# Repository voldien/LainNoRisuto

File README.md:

# LainNoRisuto

Just a collection of electronic schematic and board layouts.

## ARM ToolChain

```bash
```

## AVR ToolChain

```bash
sudo apt-get install gcc-avr binutils-avr avr-libc gdb-avr avrdude
```

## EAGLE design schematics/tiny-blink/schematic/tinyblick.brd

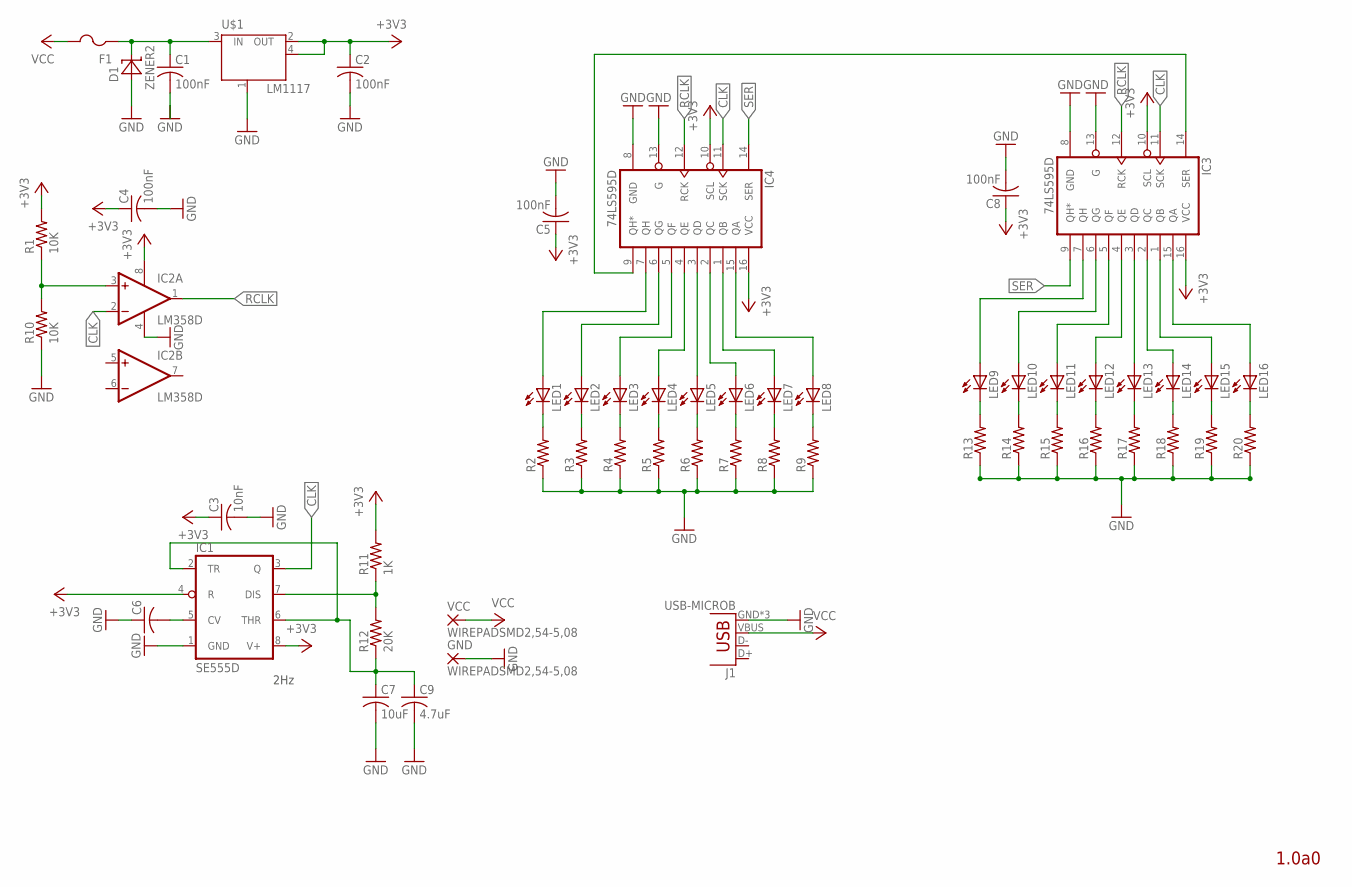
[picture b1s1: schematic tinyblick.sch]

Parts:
C1, C2, C4, C5, C8: 100nF; C0603
C3: 10nF; C0603
C6: C-USC0603; C0603
C7: 10uF; C0603
C9: 4.7uF; C0603
D1: ZENER2; SOD123
F1: PTCFUSE-1206; R1206
GND: WIREPADSMD2,54-5,08; SMD2,54-5,08
IC1: SE555D; SO08
IC2: LM358D; SO08
IC3, IC4: 74LS595D; SO16
J1: USB-MICROB
LED1, LED2, LED3, LED4, LED5, LED6, LED7, LED8, LED9, LED10, LED11, LED12, LED13, LED14, LED15, LED16: LEDCHIP-LED0603; CHIP-LED0603
R1, R10: 10K; R0603
R2, R3, R4, R5, R6, R7, R8, R9, R13, R14, R15, R16, R17, R18, R19, R20: R-US_R0603; R0603
R11: 1K; R0603
R12: 20K; R0603
U$1: LM1117; SOT223
VCC: WIREPADSMD2,54-5,08; SMD2,54-5,08

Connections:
+3V3: C2.1, C3.1, C4.1, C5.1, C8.1, IC1.4 (R), IC1.8 (V+), IC2.8 (V+), IC3.10 (SCL), IC3.16 (VCC), IC4.10 (SCL), IC4.16 (VCC), R1.2, R11.2, U$1.2 (OUT), U$1.4 (OUT)
CLK: IC1.3 (Q), IC2.2 (-IN), IC3.11 (SCK), IC4.11 (SCK)
GND: C1.2, C2.2, C3.2, C4.2, C5.2, C6.1, C7.2, C8.2, C9.2, D1.A, GND.1, IC1.1 (GND), IC2.4 (V-), IC3.8 (GND), IC3.13 (G), IC4.8 (GND), IC4.13 (G), J1.GND, J1.MT1 (GND), J1.MT2 (GND), R2.1, R3.1, R4.1, R5.1, R6.1, R7.1, R8.1, R9.1, R10.1, R13.1, R14.1, R15.1, R16.1, R17.1, R18.1, R19.1, R20.1, U$1.1 (GND/ADJ)
unnamed: LED1.C, R2.2
unnamed: IC1.7 (DIS), R11.1, R12.2
unnamed: LED2.C, R3.2
unnamed: C7.1, C9.1, IC1.2 (TR), IC1.6 (THR), R12.1
unnamed: LED3.C, R4.2
unnamed: LED9.C, R13.2
unnamed: LED4.C, R5.2
unnamed: LED5.C, R6.2
unnamed: IC4.3 (QD), LED5.A
unnamed: LED6.C, R7.2
unnamed: IC4.2 (QC), LED6.A
unnamed: LED7.C, R8.2
unnamed: IC4.1 (QB), LED7.A
unnamed: LED8.C, R9.2
unnamed: IC4.15 (QA), LED8.A
unnamed: IC4.7 (QH), LED1.A
unnamed: IC2.3 (+IN), R1.1, R10.2
unnamed: C1.1, D1.C, F1.1, U$1.3 (IN)
unnamed: IC4.6 (QG), LED2.A
unnamed: IC4.5 (QF), LED3.A
unnamed: C6.2, IC1.5 (CV)
unnamed: LED10.C, R14.2
unnamed: LED11.C, R15.2
unnamed: IC4.4 (QE), LED4.A
unnamed: LED12.C, R16.2
unnamed: LED13.C, R17.2
unnamed: IC3.3 (QD), LED13.A
unnamed: LED14.C, R18.2
unnamed: IC3.2 (QC), LED14.A
unnamed: LED15.C, R19.2
unnamed: IC3.1 (QB), LED15.A
unnamed: LED16.C, R20.2
unnamed: IC3.15 (QA), LED16.A
unnamed: IC3.7 (QH), LED9.A
unnamed: IC3.6 (QG), LED10.A
unnamed: IC3.5 (QF), LED11.A
unnamed: IC3.4 (QE), LED12.A
unnamed: IC3.14 (SER), IC4.9 (QH*)
RCLK: IC2.1 (OUT), IC3.12 (RCK), IC4.12 (RCK)
SER: IC3.9 (QH*), IC4.14 (SER)
VCC: F1.2, J1.VBUS, VCC.1

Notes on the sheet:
1.0a0
2Hz

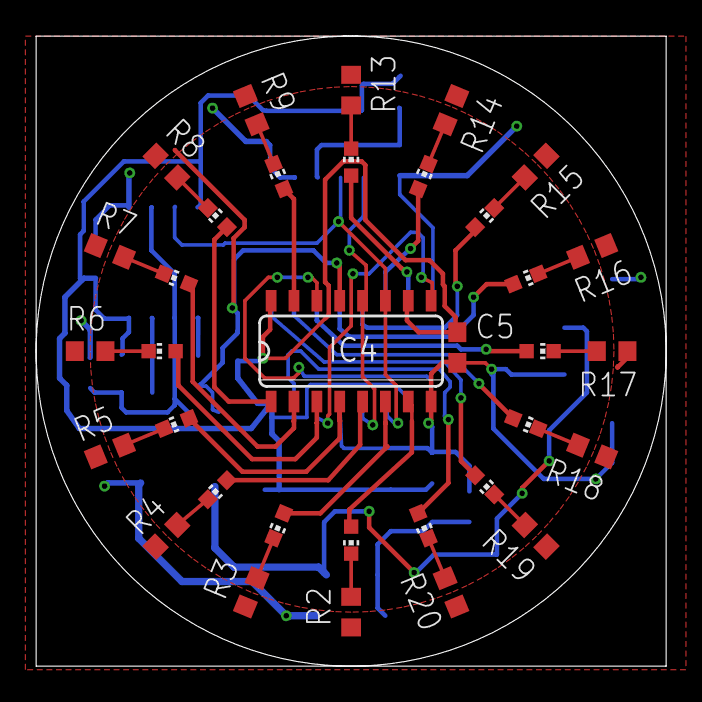
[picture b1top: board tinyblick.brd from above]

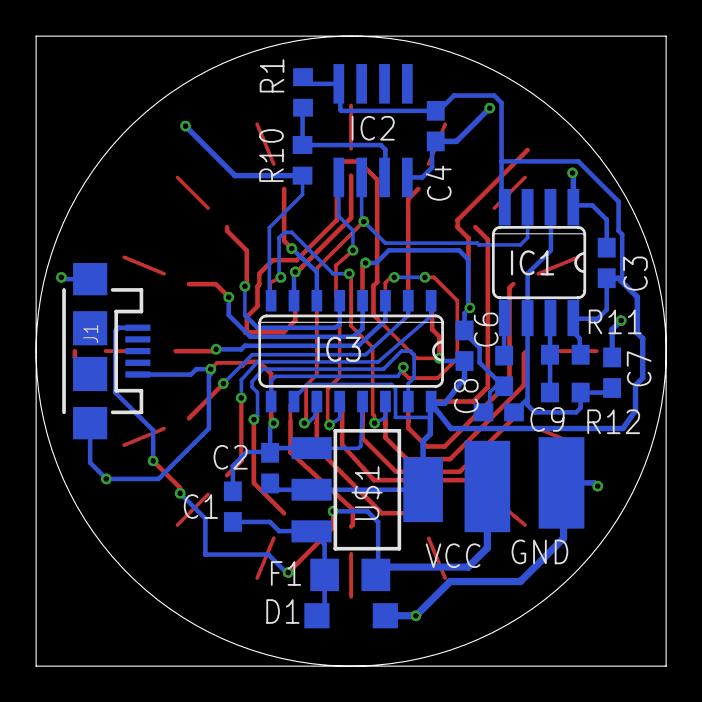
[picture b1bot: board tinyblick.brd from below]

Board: 2 copper layers, 35.0 x 35.0 mm, 55 parts (21 on the bottom side), 44 nets.

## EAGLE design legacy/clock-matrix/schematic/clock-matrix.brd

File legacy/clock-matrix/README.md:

# Binary Matrix Clock

Insipired by the binary clock in smarter every day.

## Board Layout

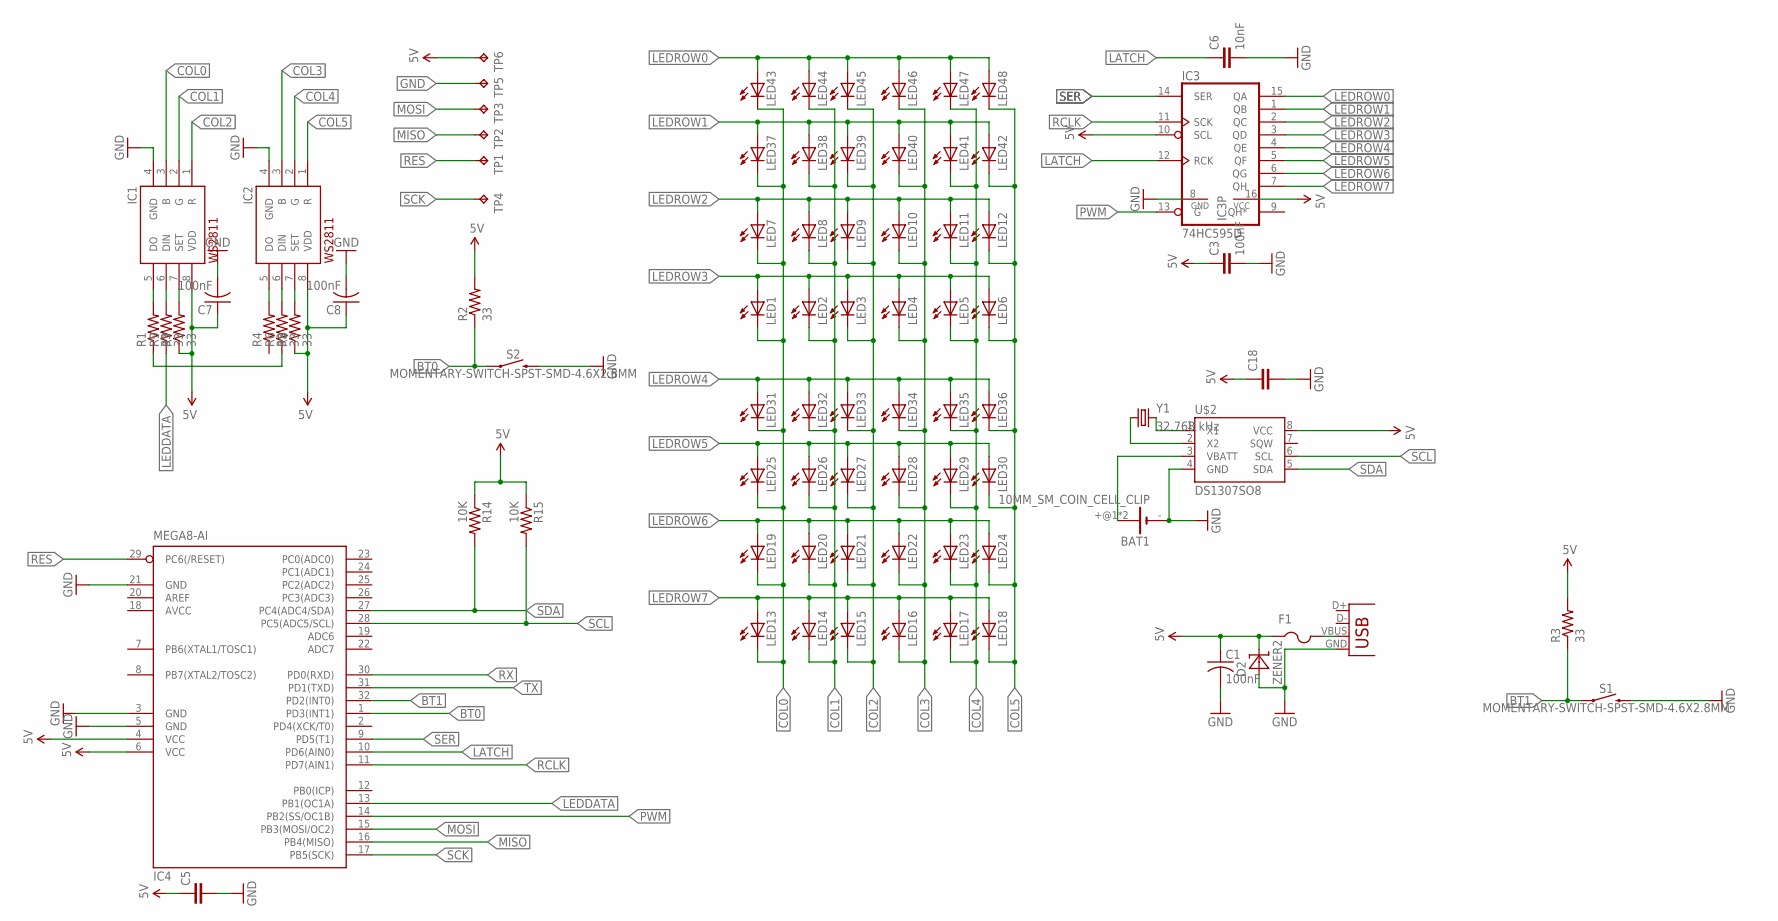
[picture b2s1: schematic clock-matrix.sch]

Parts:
BAT1: 10MM_SM_COIN_CELL_CLIP
C1, C3, C7, C8: 100nF; C0603
C5, C18: C-EUC0603; C0603
C6: 10nF; C0603
D2: ZENER2; SOD123
F1: PTCFUSE-1206; R1206
IC1, IC2: WS2811-SOP8; SO08-SKINNYPADS
IC3: 74HC595D; SO16
IC4: MEGA8-AI; TQFP32-08
LED1, LED2, LED3, LED4, LED5, LED6, LED7, LED8, LED9, LED10, LED11, LED12, LED13, LED14, LED15, LED16, LED17, LED18, LED19, LED20, LED21, LED22, LED23, LED24, LED25, LED26, LED27, LED28, LED29, LED30, LED31, LED32, LED33, LED34, LED35, LED36, LED37, LED38, LED39, LED40, LED41, LED42, LED43, LED44, LED45, LED46, LED47, LED48: LED1206; LED-1206
R1, R2, R3, R4, R6, R7, R8, R9: 33; R0603
R14, R15: 10K; R0603
S1, S2: MOMENTARY-SWITCH-SPST-SMD-4.6X2.8MM; TACTILE_SWITCH_SMD_4.6X2.8MM
TP1, TP2, TP3, TP4, TP5, TP6: TPTP10R; TP10R
U$2: DS1307SO8; SO08
X2: USB-MICROB
Y1: 32.768 kHz; TC26H

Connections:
5V: C1.1, C3.1, C5.1, C7.1, C8.1, C18.1, D2.C, F1.1, IC1.8 (VDD), IC2.8 (VDD), IC3.10 (SCL), IC3.16 (VCC), IC4.4 (VCC), IC4.6 (VCC), R2.2, R3.2, R7.1, R8.1, R14.1, R15.1, TP6.TP, U$2.8 (VCC)
AVCC: IC4.18 (AVCC)
BT0: IC4.1 (PD3(INT1)), R2.1, S2.1, S2.2 (1)
BT1: IC4.32 (PD2(INT0)), R3.1, S1.1, S1.2 (1)
COL0: IC1.3 (B), LED1.C, LED7.C, LED13.C, LED19.C, LED25.C, LED31.C, LED37.C, LED43.C
COL1: IC1.2 (G), LED2.C, LED8.C, LED14.C, LED20.C, LED26.C, LED32.C, LED38.C, LED44.C
COL2: IC1.1 (R), LED3.C, LED9.C, LED15.C, LED21.C, LED27.C, LED33.C, LED39.C, LED45.C
COL3: IC2.3 (B), LED4.C, LED10.C, LED16.C, LED22.C, LED28.C, LED34.C, LED40.C, LED46.C
COL4: IC2.2 (G), LED5.C, LED11.C, LED17.C, LED23.C, LED29.C, LED35.C, LED41.C, LED47.C
COL5: IC2.1 (R), LED6.C, LED12.C, LED18.C, LED24.C, LED30.C, LED36.C, LED42.C, LED48.C
GND: BAT1.-, C1.2, C3.2, C5.2, C6.2, C7.2, C8.2, C18.2, D2.A, IC1.4 (GND), IC2.4 (GND), IC3.8 (GND), IC4.3 (GND), IC4.5 (GND), IC4.21 (GND), S1.3 (2), S1.4 (2), S2.3 (2), S2.4 (2), TP5.TP, U$2.4 (GND), X2.GND
LATCH: C6.1, IC3.12 (RCK), IC4.10 (PD6(AIN0))
LEDDATA: IC4.13 (PB1(OC1A)), R9.1
LEDROW0: IC3.15 (QA), LED43.A, LED44.A, LED45.A, LED46.A, LED47.A, LED48.A
LEDROW1: IC3.1 (QB), LED37.A, LED38.A, LED39.A, LED40.A, LED41.A, LED42.A
LEDROW2: IC3.2 (QC), LED7.A, LED8.A, LED9.A, LED10.A, LED11.A, LED12.A
LEDROW3: IC3.3 (QD), LED1.A, LED2.A, LED3.A, LED4.A, LED5.A, LED6.A
LEDROW4: IC3.4 (QE), LED31.A, LED32.A, LED33.A, LED34.A, LED35.A, LED36.A
LEDROW5: IC3.5 (QF), LED25.A, LED26.A, LED27.A, LED28.A, LED29.A, LED30.A
LEDROW6: IC3.6 (QG), LED19.A, LED20.A, LED21.A, LED22.A, LED23.A, LED24.A
LEDROW7: IC3.7 (QH), LED13.A, LED14.A, LED15.A, LED16.A, LED17.A, LED18.A
MISO: IC4.16 (PB4(MISO)), TP2.TP
MOSI: IC4.15 (PB3(MOSI/OC2)), TP3.TP
unnamed: R1.1, R6.1
unnamed: IC1.5 (DO), R1.2
unnamed: IC2.6 (DIN), R6.2
unnamed: IC1.7 (SET), R7.2
unnamed: IC2.5 (DO), R4.2
unnamed: IC1.6 (DIN), R9.2
unnamed: BAT1.+@1 (+), BAT1.+@2 (+), U$2.3 (VBATT)
unnamed: U$2.2 (X2), Y1.1
unnamed: U$2.1 (X1), Y1.2
unnamed: IC2.7 (SET), R8.2
unnamed: F1.2, X2.VBUS
PWM: IC3.13 (G), IC4.14 (PB2(SS/OC1B))
RCLK: IC3.11 (SCK), IC4.11 (PD7(AIN1))
RES: IC4.29 (PC6(/RESET)), TP1.TP
RX: IC4.30 (PD0(RXD))
SCK: IC4.17 (PB5(SCK)), TP4.TP
SCL: IC4.28 (PC5(ADC5/SCL)), R15.2, U$2.6 (SCL)
SDA: IC4.27 (PC4(ADC4/SDA)), R14.2, U$2.5 (SDA)
SER: IC3.14 (SER), IC4.9 (PD5(T1))
TX: IC4.31 (PD1(TXD))

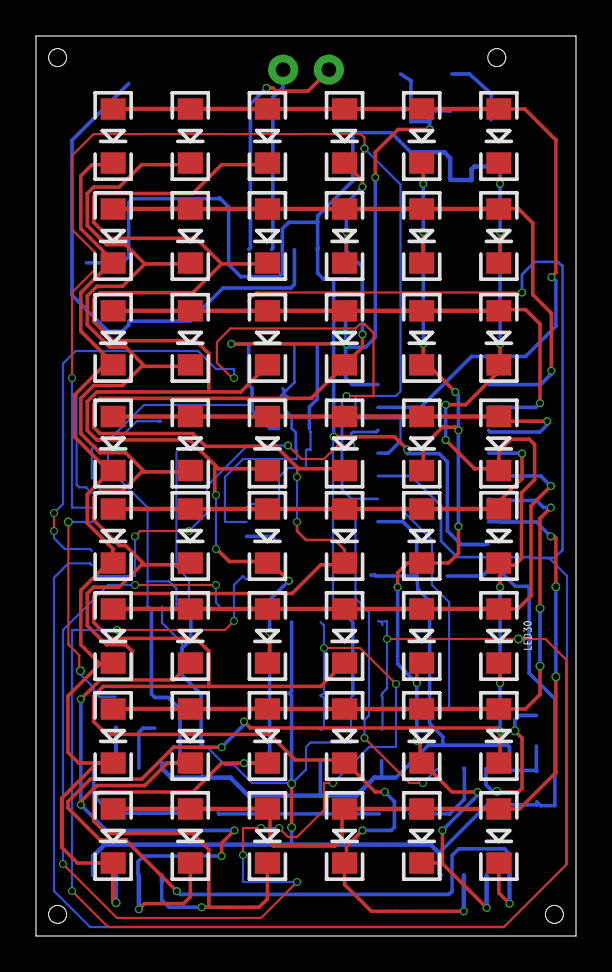
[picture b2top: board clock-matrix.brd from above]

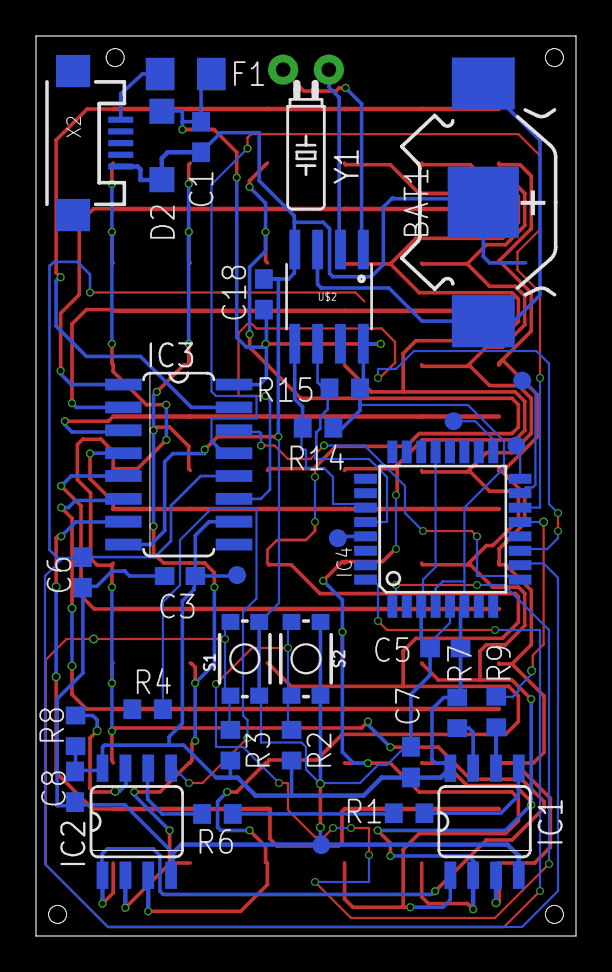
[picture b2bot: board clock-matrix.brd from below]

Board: 2 copper layers, 30.0 x 50.0 mm, 83 parts (35 on the bottom side), 40 nets.

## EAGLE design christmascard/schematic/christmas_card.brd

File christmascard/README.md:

# Christmas LED Board

Remark that the schematic and PCB layout and the software driver are still work in progress and still have bugs both in the hardware and software.

# Motivation
Create a pcb board that could act as a christmas card.

## Installation

### Unix
The driver for *UNIX* system can be installed as followed:
```
make 
make install
```

# License
The source code for this project is licensed under the GPL+3 License - see the [LICENSE](LICENSE) file for details.
The hardware design for this project is under the OSHW License - See  for more detials.

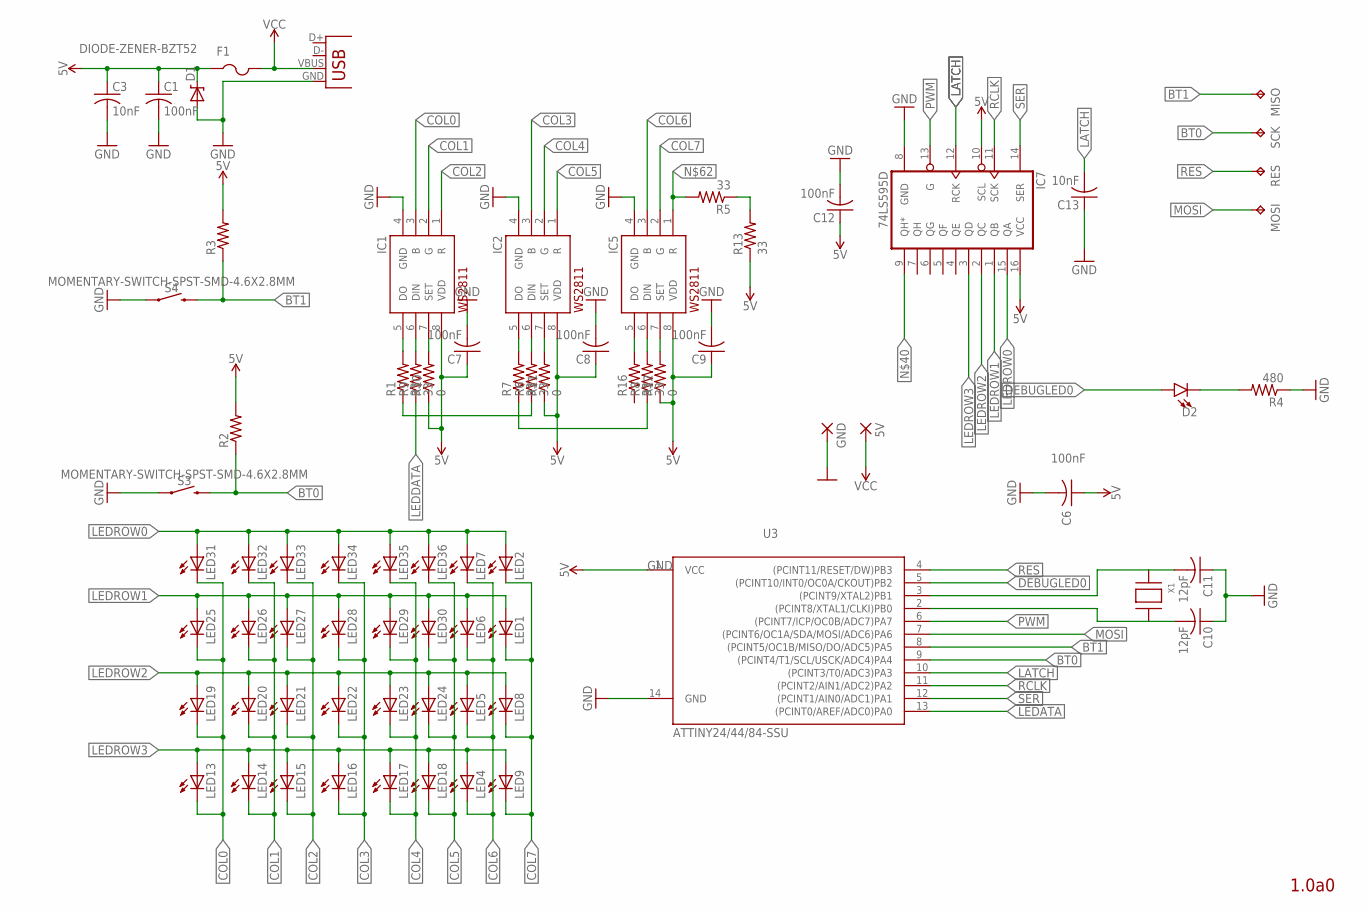
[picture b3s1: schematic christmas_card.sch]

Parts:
5V: WIREPADSMD2,54-5,08; SMD2,54-5,08
C1, C6, C7, C8, C9, C12: 100nF; C0603
C3, C13: 10nF; C0603
C10, C11: 12pF; C0603
D1: DIODE-ZENER-BZT52; SOD-323
D2: LED0603; LED-0603
F1: PTCFUSE-1206; R1206
GND: WIREPADSMD2,54-5,08; SMD2,54-5,08
IC1, IC2, IC5: WS2811-SOP8; SO08-SKINNYPADS
IC7: 74LS595D; SO16
LED1, LED2, LED4, LED5, LED6, LED7, LED8, LED9, LED13, LED14, LED15, LED16, LED17, LED18, LED19, LED20, LED21, LED22, LED23, LED24, LED25, LED26, LED27, LED28, LED29, LED30, LED31, LED32, LED33, LED34, LED35, LED36: LED1206; LED-1206
MISO: TPB1,27; B1,27
MOSI: TPB1,27; B1,27
R1, R5, R6, R7, R8, R9, R13, R16: 33; R0603
R2, R3: R-US_R0603; R0603
R4: 480; R0603
R10, R11, R12: 0; R0603
RES: TPB1,27; B1,27
S3, S4: MOMENTARY-SWITCH-SPST-SMD-4.6X2.8MM; TACTILE_SWITCH_SMD_4.6X2.8MM
SCK: TPB1,27; B1,27
U3: ATTINY24/44/84-SSU; SOIC14N
X1: XTALNX5032; NX5032
X2: USB-MICROB

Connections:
5V: C1.1, C3.1, C6.1, C7.1, C8.1, C9.1, C12.1, D1.1 (C), F1.1, IC1.8 (VDD), IC2.8 (VDD), IC5.8 (VDD), IC7.10 (SCL), IC7.16 (VCC), R2.2, R3.2, R10.1, R11.1, R12.1, R13.1, U3.1 (VCC)
BT0: R2.1, S3.3 (2), S3.4 (2), SCK.TP, U3.9 ((PCINT4/T1/SCL/USCK/ADC4)PA4)
BT1: MISO.TP, R3.1, S4.3 (2), S4.4 (2), U3.8 ((PCINT5/OC1B/MISO/DO/ADC5)PA5)
COL0: IC1.3 (B), LED13.C, LED19.C, LED25.C, LED31.C
COL1: IC1.2 (G), LED14.C, LED20.C, LED26.C, LED32.C
COL2: IC1.1 (R), LED15.C, LED21.C, LED27.C, LED33.C
COL3: IC2.3 (B), LED16.C, LED22.C, LED28.C, LED34.C
COL4: IC2.2 (G), LED17.C, LED23.C, LED29.C, LED35.C
COL5: IC2.1 (R), LED18.C, LED24.C, LED30.C, LED36.C
COL6: IC5.3 (B), LED4.C, LED5.C, LED6.C, LED7.C
COL7: IC5.2 (G), LED1.C, LED2.C, LED8.C, LED9.C
DEBUGLED0: D2.A, U3.5 ((PCINT10/INT0/OC0A/CKOUT)PB2)
GND: C1.2, C3.2, C6.2, C7.2, C8.2, C9.2, C10.1, C11.1, C12.2, C13.1, D1.2 (A), GND.1, IC1.4 (GND), IC2.4 (GND), IC5.4 (GND), IC7.8 (GND), R4.1, S3.1, S3.2 (1), S4.1, S4.2 (1), U3.14 (GND), X2.GND
LATCH: C13.2, IC7.12 (RCK), U3.10 ((PCINT3/T0/ADC3)PA3)
LEDROW0: IC7.15 (QA), LED2.A, LED7.A, LED31.A, LED32.A, LED33.A, LED34.A, LED35.A, LED36.A
LEDROW1: IC7.1 (QB), LED1.A, LED6.A, LED25.A, LED26.A, LED27.A, LED28.A, LED29.A, LED30.A
LEDROW2: IC7.2 (QC), LED5.A, LED8.A, LED19.A, LED20.A, LED21.A, LED22.A, LED23.A, LED24.A
LEDROW3: IC7.3 (QD), LED4.A, LED9.A, LED13.A, LED14.A, LED15.A, LED16.A, LED17.A, LED18.A
MOSI: MOSI.TP, U3.7 ((PCINT6/OC1A/SDA/MOSI/ADC6)PA6)
unnamed: R1.1, R6.1
unnamed: IC1.5 (DO), R1.2
unnamed: IC2.6 (DIN), R6.2
unnamed: IC2.5 (DO), R7.2
unnamed: R7.1, R8.1
unnamed: IC5.6 (DIN), R8.2
unnamed: IC1.6 (DIN), R9.2
unnamed: IC5.7 (SET), R12.2
unnamed: D2.C, R4.2
unnamed: C10.2, U3.2 ((PCINT8/XTAL1/CLKI)PB0), X1.P$2
unnamed: IC5.5 (DO), R16.2
unnamed: R5.1, R13.2
unnamed: C11.2, U3.3 ((PCINT9/XTAL2)PB1), X1.P$1
unnamed: IC2.7 (SET), R11.2
unnamed: IC1.7 (SET), R10.2
unnamed: IC5.1 (R), R5.2
PWM: IC7.13 (G), U3.6 ((PCINT7/ICP/OC0B/ADC7)PA7)
RCLK: IC7.11 (SCK), U3.11 ((PCINT2/AIN1/ADC2)PA2)
RES: RES.TP, U3.4 ((PCINT11/RESET/DW)PB3)
SER: IC7.14 (SER), U3.12 ((PCINT1/AIN0/ADC1)PA1)
VCC: 5V.1, F1.2, X2.VBUS

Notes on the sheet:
1.0a0

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
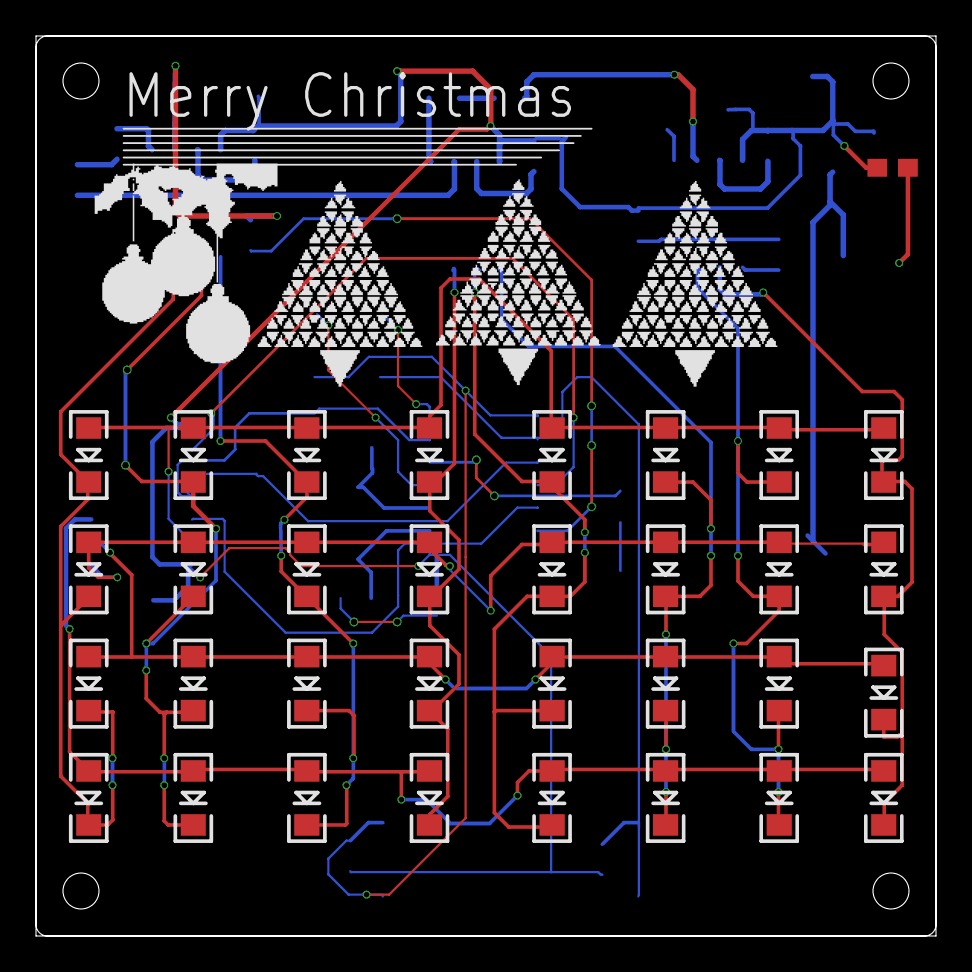
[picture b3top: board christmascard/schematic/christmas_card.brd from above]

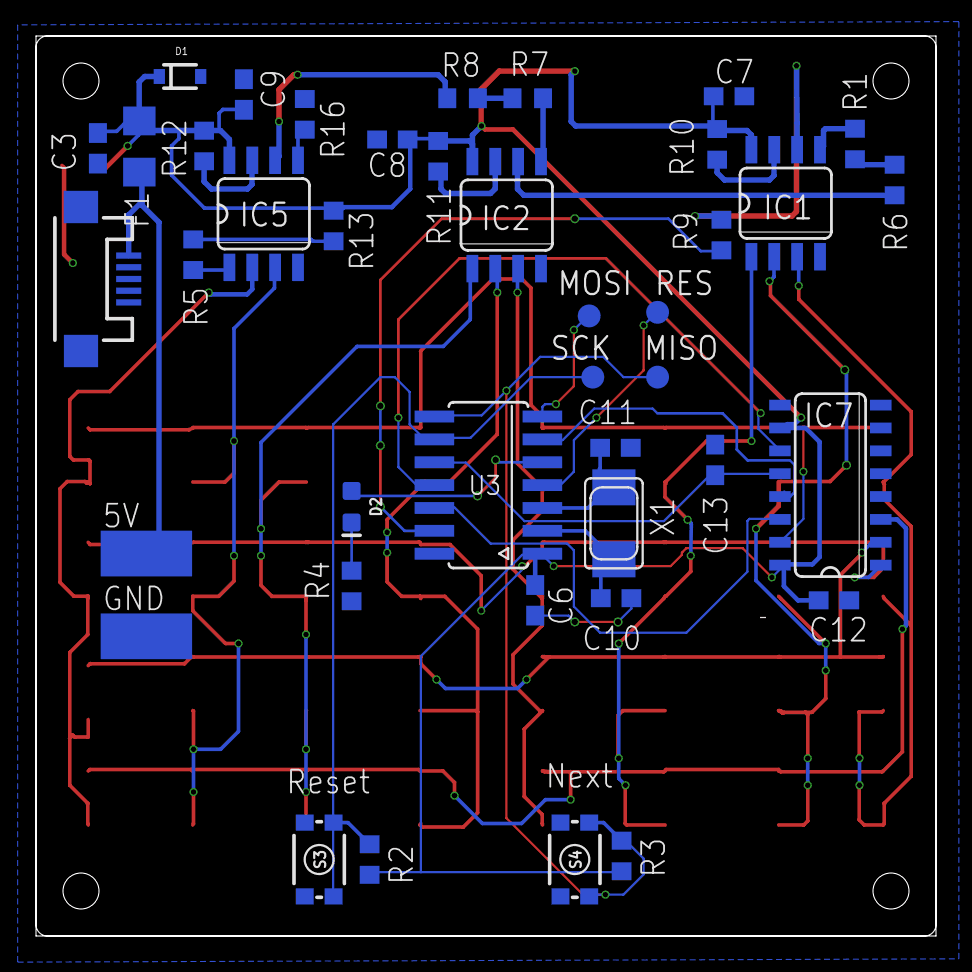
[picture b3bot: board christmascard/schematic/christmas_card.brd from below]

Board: 2 copper layers, 50.0 x 50.0 mm, 74 parts (41 on the bottom side), 41 nets.

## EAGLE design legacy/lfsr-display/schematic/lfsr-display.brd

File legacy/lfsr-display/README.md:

ledboard
---
ledboard is as the name implies. A board for driving LED's. It was influcended by IKEA's LED strip that useage Alkine battery. Even though LED's are power effiecent it's still a waste of material of needing to replace these batteries.
That's why this ledboard has support to use either lithium ion battery for portability or via USB. 

Features
---
SPI pins.
LED pads.
Battery Pads.
Attiny13

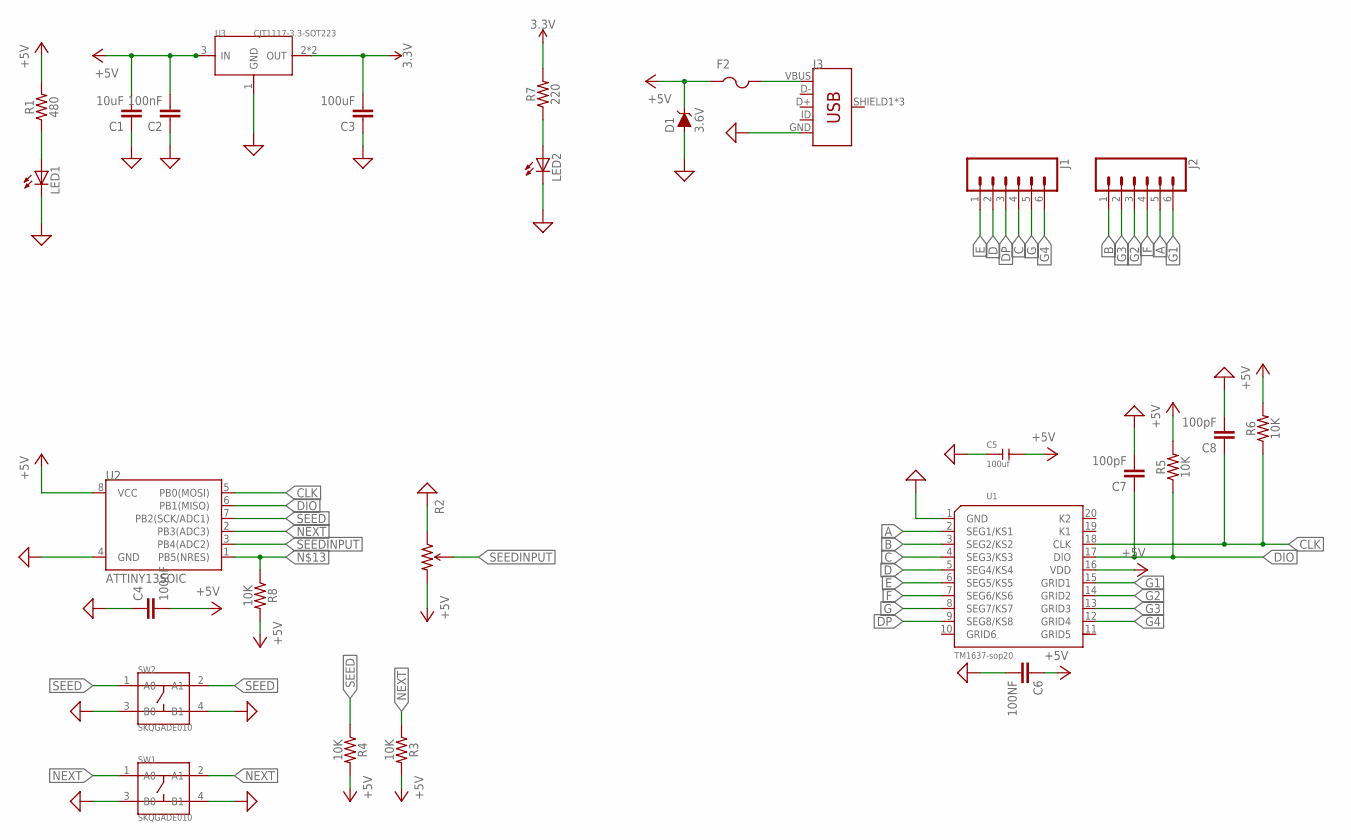
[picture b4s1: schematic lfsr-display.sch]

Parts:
C1: 10uF; RESC0603_L
C2, C4: 100nF; RESC0603_L
C3: 100uF; RESC0603_L
C5: 100uf; C1206
C6: 100NF; RESC0603_L
C7, C8: 100pF; RESC0603_L
D1: 3.6V; SOD-323
F2: PTCFUSE-1206; R1206
J1, J2: CONN_06NO_SILK_FEMALE_PTH; 1X06_NO_SILK
J3: USB_MICRO-BREDUCED_PASTE; USB-B-MICRO-SMD_RED_PASTE
LED1, LED2: LEDCHIP-LED0603; CHIP-LED0603
R1: 480; 0603
R2: TRIMPOT; TRIMPOT-5MM-V2
R3, R4, R5, R6, R8: 10K; 0603
R7: 220; 0603
SW1, SW2: SKQGADE010; SW4-SMD-5.2X5.2X1.5MM
U1: TM1637-sop20; SOP20-1.27-12.7X7.65MM
U2: ATTINY13SOIC; SO08_MCU
U3: CJT1117-3.3-SOT223; SOT-223

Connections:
3.3V: C3.2, R7.2, U3.2 (OUT), U3.TER (OUT)
+5V: C1.2, C2.2, C4.2, C5.2, C6.1, D1.C, F2.1, R1.2, R2.C (CW), R3.2, R4.2, R5.2, R6.2, R8.2, U1.16 (VDD), U2.8 (VCC), U3.3 (IN)
A: J2.5, U1.2 (SEG1/KS1)
B: J2.1, U1.3 (SEG2/KS2)
C: J1.4, U1.4 (SEG3/KS3)
CLK: C8.1, R6.1, U1.18 (CLK), U2.5 (PB0(MOSI))
D: J1.2, U1.5 (SEG4/KS4)
DIO: C7.1, R5.1, U1.17 (DIO), U2.6 (PB1(MISO))
DP: J1.3, U1.9 (SEG8/KS8)
E: J1.1, U1.6 (SEG5/KS5)
F: J2.4, U1.7 (SEG6/KS6)
G: J1.5, U1.8 (SEG7/KS7)
G1: J2.6, U1.15 (GRID1)
G2: J2.3, U1.14 (GRID2)
G3: J2.2, U1.13 (GRID3)
G4: J1.6, U1.12 (GRID4)
GND: C1.1, C2.1, C3.1, C4.1, C5.1, C6.2, C7.2, C8.2, D1.A, J3.GND, LED1.C, LED2.C, R2.A (CCW), SW1.3 (B0), SW1.4 (B1), SW2.3 (B0), SW2.4 (B1), U1.1 (GND), U2.4 (GND), U3.1 (GND)
unnamed: LED1.A, R1.1
unnamed: LED2.A, R7.1
unnamed: F2.2, J3.VBUS
unnamed: R8.1, U2.1 (PB5(NRES))
NEXT: R3.1, SW1.1 (A0), SW1.2 (A1), U2.2 (PB3(ADC3))
SEED: R4.1, SW2.1 (A0), SW2.2 (A1), U2.7 (PB2(SCK/ADC1))
SEEDINPUT: R2.B (WIPER), U2.3 (PB4(ADC2))

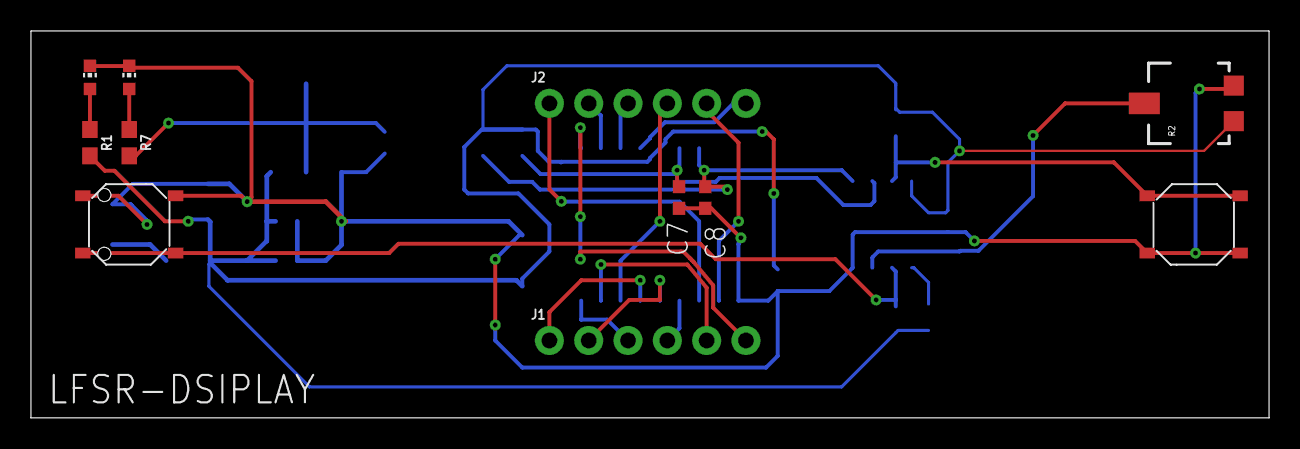
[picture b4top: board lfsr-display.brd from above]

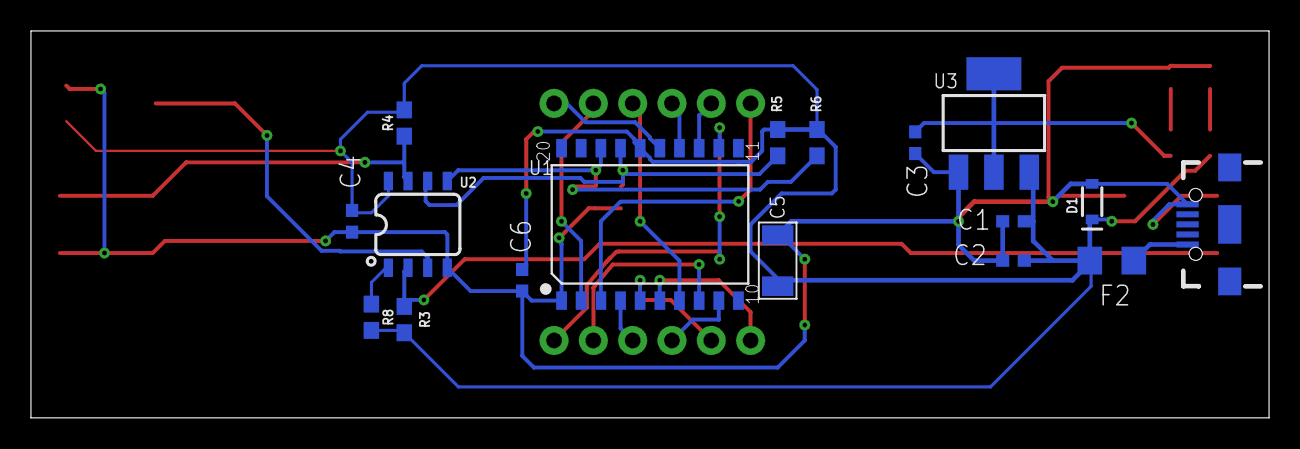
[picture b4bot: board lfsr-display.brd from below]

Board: 2 copper layers, 80.0 x 25.0 mm, 28 parts (17 on the bottom side), 24 nets.

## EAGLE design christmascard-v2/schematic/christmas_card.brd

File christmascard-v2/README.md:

# Christmas LED Board

Remark that the schematic and PCB layout and the software driver are still work in progress and still have bugs both in the hardware and software.

# Motivation

## Installation

### Unix
The driver for *UNIX* system can be installed as followed:
```
make 
make install
```

# License
The source code for this project is licensed under the GPL+3 License - see the [LICENSE](LICENSE) file for details.
The hardware design for this project is under the OSHW License - See  for more detials.

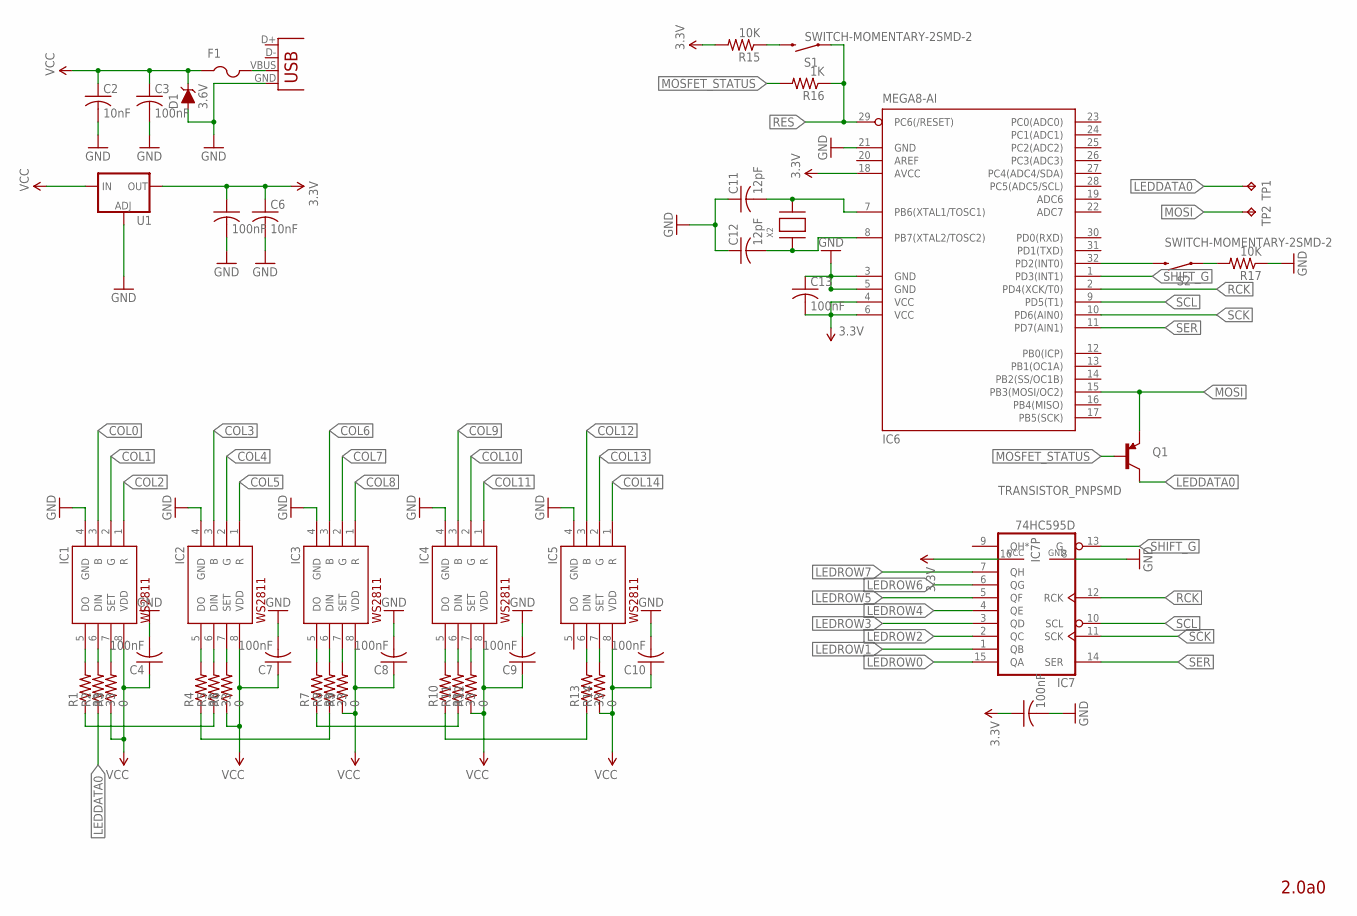
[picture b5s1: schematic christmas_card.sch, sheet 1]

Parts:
C2, C6: 10nF; C0603
C3, C4, C5, C7, C8, C9, C10, C13, C14: 100nF; C0603
C11, C12: 12pF; C0603
D1: 3.6V; SOD-323
F1: PTCFUSE-1206; R1206
IC1, IC2, IC3, IC4, IC5: WS2811-SOP8; SO08-SKINNYPADS
IC6: MEGA8-AI; TQFP32-08
IC7: 74HC595D; SO16
Q1: TRANSISTOR_PNPSMD; SOT23-3
R1, R2, R4, R5, R7, R8, R10, R11, R13: 33; R0603
R3, R6, R9, R12, R14: 0; R0603
R15, R17: 10K; R0603
R16: 1K; R0603
S1, S2: SWITCH-MOMENTARY-2SMD-2; TACTILE_SWITCH_SMD-2
TP1, TP2: TPB1,27; B1,27
U1: V_REG_LM1117SOT223; SOT223
X1: USB-MICROB
X2: XTALNX5032; NX5032

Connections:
3.3V: C5.1, C6.1, C13.2, C14.1, IC6.4 (VCC), IC6.6 (VCC), IC6.18 (AVCC), IC7.16 (VCC), R15.2, U1.2 (OUT), U1.4 (OUT)
COL0: IC1.3 (B); also elsewhere on the board
COL1: IC1.2 (G); also elsewhere on the board
COL2: IC1.1 (R); also elsewhere on the board
COL3: IC2.3 (B); also elsewhere on the board
COL4: IC2.2 (G); also elsewhere on the board
COL5: IC2.1 (R); also elsewhere on the board
COL6: IC3.3 (B); also elsewhere on the board
COL7: IC3.2 (G); also elsewhere on the board
COL8: IC3.1 (R); also elsewhere on the board
COL9: IC4.3 (B); also elsewhere on the board
COL10: IC4.2 (G); also elsewhere on the board
COL11: IC4.1 (R); also elsewhere on the board
COL12: IC5.3 (B); also elsewhere on the board
COL13: IC5.2 (G); also elsewhere on the board
COL14: IC5.1 (R); also elsewhere on the board
GND: C2.2, C3.2, C4.2, C5.2, C6.2, C7.2, C8.2, C9.2, C10.2, C11.1, C12.1, C13.1, C14.2, D1.A, IC1.4 (GND), IC2.4 (GND), IC3.4 (GND), IC4.4 (GND), IC5.4 (GND), IC6.3 (GND), IC6.5 (GND), IC6.21 (GND), IC7.8 (GND), R17.1, U1.1 (ADJ), X1.GND
LEDATA1: R7.1, R11.1
LEDDATA0: Q1.3 (C), R2.1, TP1.TP
LEDROW0: IC7.15 (QA); also elsewhere on the board
LEDROW1: IC7.1 (QB); also elsewhere on the board
LEDROW2: IC7.2 (QC); also elsewhere on the board
LEDROW3: IC7.3 (QD); also elsewhere on the board
LEDROW4: IC7.4 (QE); also elsewhere on the board
LEDROW5: IC7.5 (QF); also elsewhere on the board
LEDROW6: IC7.6 (QG); also elsewhere on the board
LEDROW7: IC7.7 (QH); also elsewhere on the board
MOSFET_STATUS: Q1.1 (B), R16.2
MOSI: IC6.15 (PB3(MOSI/OC2)), Q1.2 (E), TP2.TP
unnamed: R1.1, R5.1
unnamed: IC1.5 (DO), R1.2
unnamed: IC2.6 (DIN), R5.2
unnamed: IC2.5 (DO), R4.2
unnamed: R4.1, R8.1
unnamed: IC3.6 (DIN), R8.2
unnamed: IC1.6 (DIN), R2.2
unnamed: IC3.7 (SET), R9.2
unnamed: R15.1, S1.1 (2)
unnamed: C11.2, IC6.7 (PB6(XTAL1/TOSC1)), X2.P$2
unnamed: IC6.32 (PD2(INT0)), S2.1 (2)
unnamed: R17.2, S2.2 (1)
unnamed: C12.2, IC6.8 (PB7(XTAL2/TOSC2)), X2.P$1
unnamed: R10.1, R13.1
unnamed: IC4.6 (DIN), R11.2
unnamed: IC4.7 (SET), R12.2
unnamed: IC3.5 (DO), R7.2
unnamed: IC2.7 (SET), R6.2
unnamed: IC1.7 (SET), R3.2
unnamed: IC5.6 (DIN), R13.2
unnamed: IC5.7 (SET), R14.2
unnamed: F1.2, X1.VBUS
unnamed: IC4.5 (DO), R10.2
RCK: IC6.2 (PD4(XCK/T0)), IC7.12 (RCK)
RES: IC6.29 (PC6(/RESET)), R16.1, S1.2 (1)
SCK: IC6.10 (PD6(AIN0)), IC7.11 (SCK)
SCL: IC6.9 (PD5(T1)), IC7.10 (SCL)
SER: IC6.11 (PD7(AIN1)), IC7.14 (SER)
SHIFT_G: IC6.1 (PD3(INT1)), IC7.13 (G)
VCC: C2.1, C3.1, C4.1, C7.1, C8.1, C9.1, C10.1, D1.C, F1.1, IC1.8 (VDD), IC2.8 (VDD), IC3.8 (VDD), IC4.8 (VDD), IC5.8 (VDD), R3.1, R6.1, R9.1, R12.1, R14.1, U1.3 (IN)

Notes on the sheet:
2.0a0

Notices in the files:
parts and their libraries:
SparkFun-DigitalIC: Licensing: Creative Commons ShareAlike 4.0 International - https://creativecommons.org/licenses/by-sa/4.0
SparkFun: Licensing: CC v3.0 Share-Alike You are welcome to use this library for commercial purposes.
